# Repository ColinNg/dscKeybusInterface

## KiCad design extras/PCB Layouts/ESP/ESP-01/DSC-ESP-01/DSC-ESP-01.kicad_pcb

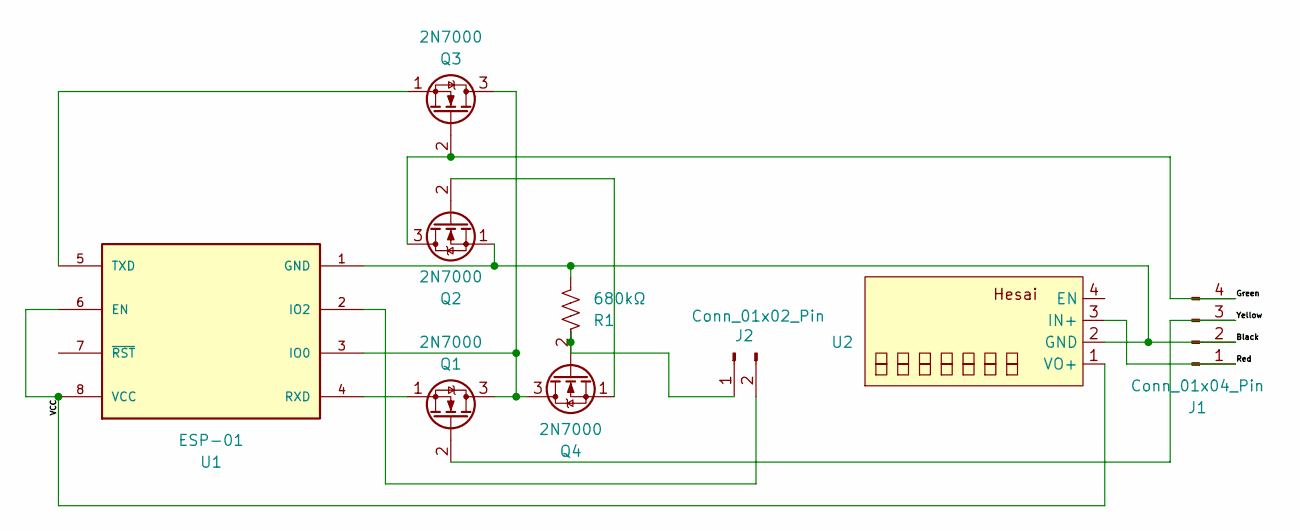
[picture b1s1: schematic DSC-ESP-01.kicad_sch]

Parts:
J1: Conn_01x04_Pin; JST_XH_B4B-XH-A_1x04_P2.50mm_Vertical
J2: Conn_01x02_Pin; PinHeader_1x02_P2.54mm_Horizontal
Q1, Q2, Q3, Q4: 2N7000; TO-92_Inline
R1: 680kΩ; R_Axial_DIN0204_L3.6mm_D1.6mm_P5.08mm_Horizontal
U1: ESP-01; ESP-01 No Keepout; PARTREV V1.2
U2: Converter_DCDC_Hesai_Mini

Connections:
/Black: J1.2, Q2.1 (S), R1.2, U1.1 (GND), U2.2 (GND)
/Green: J1.4, Q2.3 (D), Q3.2 (G)
/Red: J1.1, U2.3 (IN+)
/VCC: U1.6 (EN), U1.8 (VCC), U2.1 (VO+)
/Yellow: J1.3, Q1.2 (G)
unnamed: J2.1, Q4.2 (G), R1.1
unnamed: J2.2, U1.2 (IO2)
unnamed: Q1.3 (D), Q3.3 (D), Q4.3 (D), U1.3 (IO0)
unnamed: Q1.1 (S), U1.4 (RXD)
unnamed: Q2.2 (G), Q4.1 (S)
unnamed: Q3.1 (S), U1.5 (TXD)

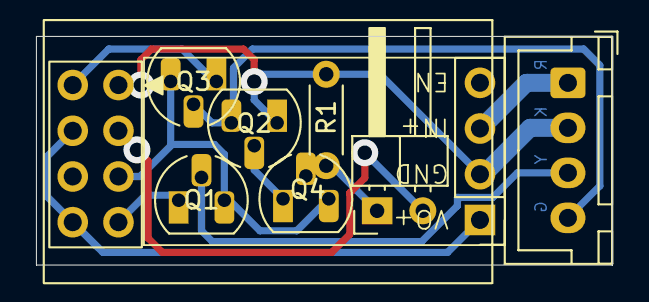
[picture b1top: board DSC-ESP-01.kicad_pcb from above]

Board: 2 copper layers, 32.0 x 12.7 mm, 9 parts (0 on the bottom side), 11 nets.

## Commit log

2018-08-18 Moved secrets to Secrets.h. Comment about a connected but unused Write pin causing problems.
2018-08-19 Sending Arm/Disarm status over Twilio. Also echoing status over serial.
2018-08-19 Adding keypad write for partition 1.
2018-08-19 Also echoing Pushed messages over serial
2018-08-19 Moved "Security system " text to a variable. Report partition in disarmed message.
2018-08-19 Fixed compilation issues. Added a string to flash.
2018-08-19 Adding in WiFi Manager for on-site configuration. Adding in OTA Update support for on-site updates.
2019-11-08 Use the recommended pins (low on startup).
2019-11-08 Cleanup.
2019-11-08 Moved "Security system " text to a variable.
2019-11-08 Echo status over serial.
2019-11-08 Moved 2 strings to flash.
2019-12-02 Moved sendPush, appendPartition, and printTimestamp to be before setup, because the Arduino 1.9.0-beta (needed for macOS Catalina compatibility) fails to compile otherwise.
2022-01-17 Made this work on the ESP01, which does not have enough pins to have both dscWrite and Serial.
2022-01-22 Found out the HIGH on startup caused the input transistors to "listen" and thus cause other pins to go HIGH, crashing on startup. Switched the enableTransistorsPin to one that defauls to LOW on boot,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
2025-10-01 DSC-ESP-01 PCB Gerbers and Excellon Drill Files generated by KiCAD.
2025-10-01 Initial commit of DSC-ESP-01 PCB design in KiCAD.
2025-10-02 Moved traces to allow milling with a wider (or dull) bit. Changed ESP-01 landing holes to 1.0mm, and standardized other holes.
2025-10-08 Redesigned DSC-ESP-01.kicad_pcb to use the `TO-92_HandSolder` footprint.
